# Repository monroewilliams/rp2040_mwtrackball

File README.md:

# rp2040-based trackball main board

This work is based on version 2 of the "rp2040 Minimal KiCad" sample provided by the Raspberry Pi foundation [here](https://datasheets.raspberrypi.com/rp2040/Minimal-KiCAD.zip).

It is inspired by (although not directly based on) jfedor2's excellent [RP2040+PMW3360 board](https://github.com/jfedor2/rp2040-pmw3360). (Although I did borrow the USB header pinout directly from that project.)

I've modified it for the specific needs of [my trackball design](https://github.com/monroewilliams/trackball), with a few other additions that may make it useful for other experimentation as well. I intend it to pair with a [breakout board design](https://github.com/monroewilliams/pmw3360-breakout) with matching JST plugs so that off-the-shelf cables can be used for assembly (instead of the hand-built sensor cables the old design needed).

The overall dimensions of the board match the dimensions of the mini-breadboard I used in the original trackball design. This is not a coincidence. ;) 

The SPI connectors are 6 pin JST-SH (1.0mm pitch), with a pinout based on [Pmod type 2](https://en.wikipedia.org/wiki/Pmod_Interface). This should match the connectors on the sensor breakout board linked above, allowing assembly using off-the-shelf 6-pin JST-SH cables. The cables need to be straight-through, not "crossed" (i.e. connect pin 1 to pin 1, etc.). I've included two SPI connectors attached to one set of SPI pins but with distinct cable select lines (labelled SPI0.x), and a third connector attached to a second set of SPI pins (SPI1.x). The number after the decimal point is the GPIO number of the cable select pin routed to each connector. The trackball design works fine with both sensors on the same SPI bus, but I expect the second bus may be useful for other experiments (such as connecting a display), and I wanted to have some flexibility to play with that.

The button connectors are also JST-SH, but just two pins each (signal and ground), with the intention that off-the-shelf "pigtail" JST cables can be soldered to microswitches for assembly. They are labelled with the number of the GPIO pin they're connected to.

There's also an on-board surface mount piezo speaker, which my trackball design uses to generate scrolling clicks when using twist-to-scroll. It should be usable for other speaker-related duties as needed.

Additionally, I added a connector that is compatible with Adafruit's ["STEMMA QT" I2C connection](https://learn.adafruit.com/introducing-adafruit-stemma-qt/what-is-stemma), and an additional 6 pin JST-SH breakout connector for a few of the other unused pins on the rp2040 (GPIOs 26-29, which happen to be the ADC-capable pins, as well as power and ground).

The final connector is a SWD debug plug that should conform to the [Raspberry Pi 3-pin Debug Connector Specification](https://datasheets.raspberrypi.com/debug/debug-connector-specification.pdf)

And just to finish things off, I included a NeoPixel (a.k.a. WS2812) RGB LED. Adding this to the board bumps it from JLCPCB's "Economic" tier to their "Standard" tier, which is a bit more expensive, so if you're having a batch of these made and would rather go the cheaper route it can just be omitted (just choose not to place it when reviewing the BOM after upload).  This same component is sold in packs of 10 by Adafruit [here](https://www.adafruit.com/product/4684), so it could be added after the fact (assuming you're willing to hand-solder a 2mm square SMD component).

Any issues with the changes I made to this layout are solely my fault. I've attempted to maintain the spirit of the rp2040 reference design, but this is my first attempt at designing a board with a microcontroller, so it would not surprise me if it has problems. Caveat emptor, etc, etc.

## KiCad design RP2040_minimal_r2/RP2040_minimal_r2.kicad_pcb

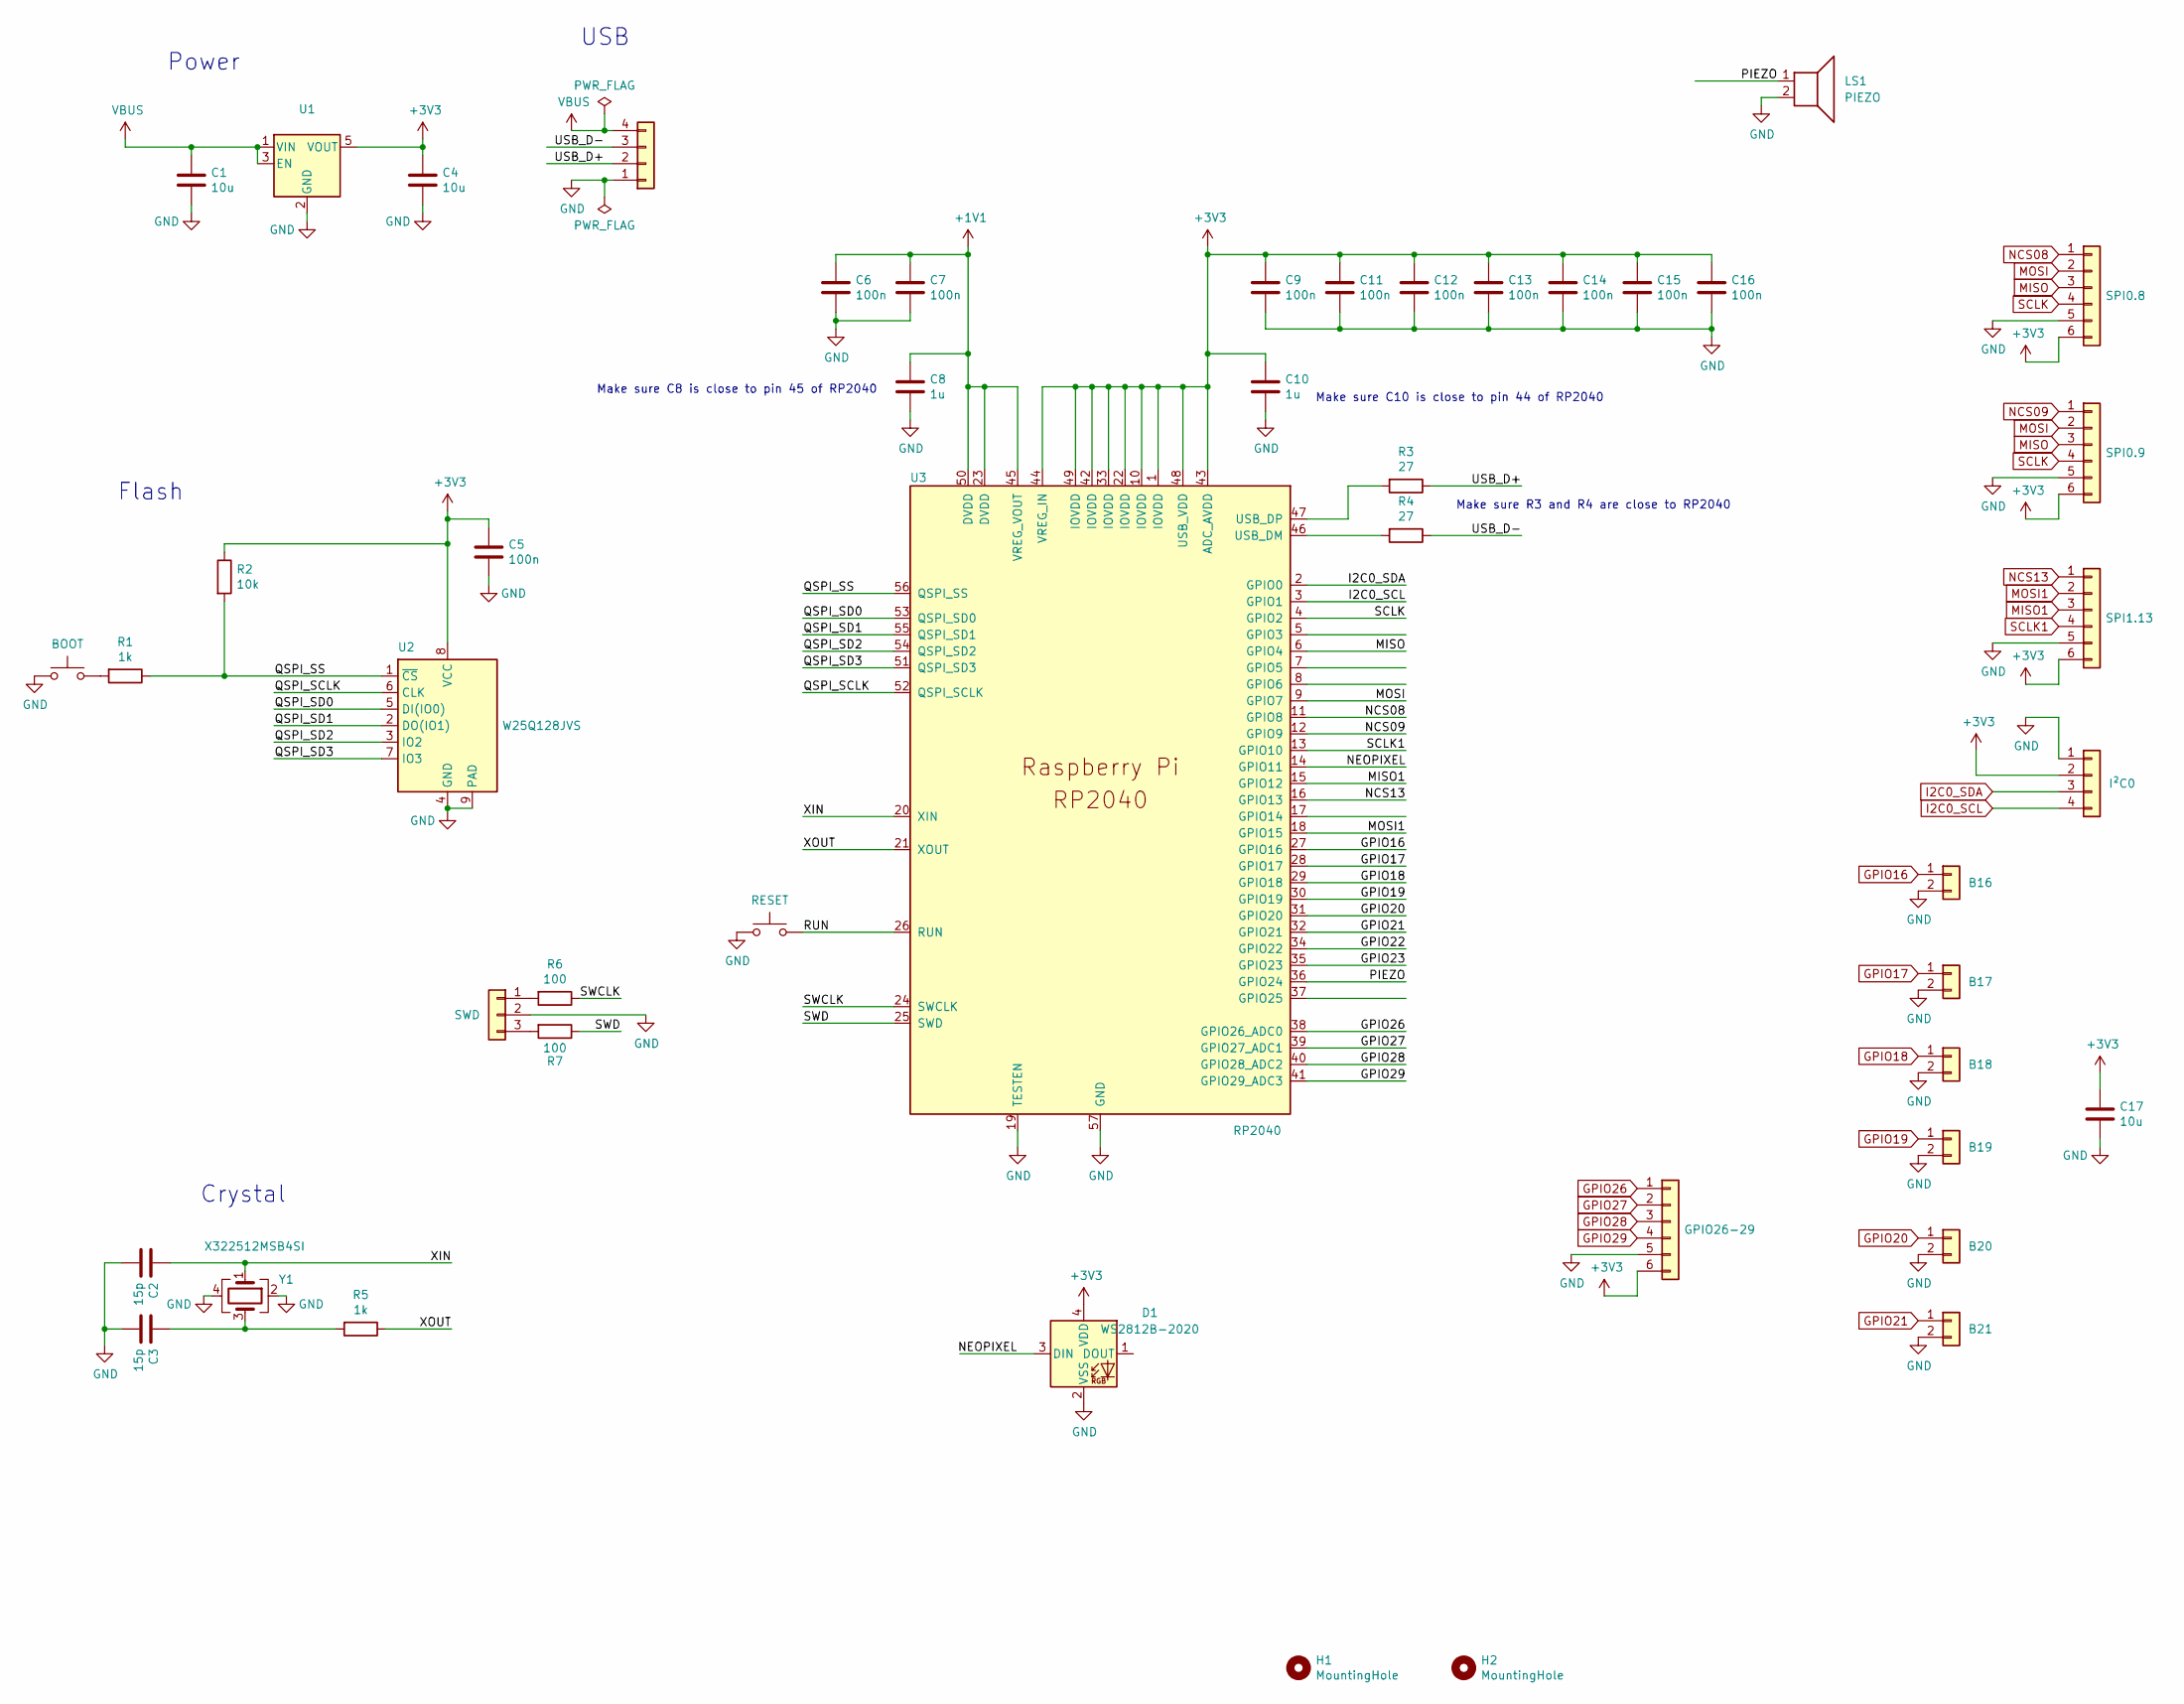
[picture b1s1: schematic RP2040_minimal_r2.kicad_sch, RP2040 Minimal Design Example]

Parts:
C1, C4, C17: 10u; C_0805_2012Metric; LCSC C15850
C2, C3: 15p; C_0402_1005Metric; LCSC C1548
C5, C6, C7, C9, C11, C12, C13, C14, C15, C16: 100n; C_0402_1005Metric; LCSC C126504
C8, C10: 1u; C_0402_1005Metric; LCSC C307331
D1: WS2812B-2020; LED_WS2812B-2020_PLCC4_2.0x2.0mm; LCSC C965555
H1, H2: MountingHole; MountingHole_2.2mm_M2
J1: SPI0.8; JST_SH_BM06B-SRSS-TB_1x06-1MP_P1.00mm_Vertical; LCSC C7430455
J2: SPI0.9; JST_SH_BM06B-SRSS-TB_1x06-1MP_P1.00mm_Vertical; LCSC C7430455
J3: SPI1.13; JST_SH_BM06B-SRSS-TB_1x06-1MP_P1.00mm_Vertical; LCSC C7430455
J4: I²C0; JST_SH_BM04B-SRSS-TB_1x04-1MP_P1.00mm_Vertical; LCSC C160390
J5: USB; JST_XH_B4B-XH-A_1x04_P2.50mm_Vertical; LCSC C7429634
J6: B16; JST_SH_BM02B-SRSS-TB_1x02-1MP_P1.00mm_Vertical; LCSC C160388
J7: B17; JST_SH_BM02B-SRSS-TB_1x02-1MP_P1.00mm_Vertical; LCSC C160388
J8: B18; JST_SH_BM02B-SRSS-TB_1x02-1MP_P1.00mm_Vertical; LCSC C160388
J9: B19; JST_SH_BM02B-SRSS-TB_1x02-1MP_P1.00mm_Vertical; LCSC C160388
J10: B20; JST_SH_BM02B-SRSS-TB_1x02-1MP_P1.00mm_Vertical; LCSC C160388
J11: B21; JST_SH_BM02B-SRSS-TB_1x02-1MP_P1.00mm_Vertical; LCSC C160388
J12: GPIO26-29; JST_SH_BM06B-SRSS-TB_1x06-1MP_P1.00mm_Vertical; LCSC C7430455
J13: SWD; JST_SH_BM03B-SRSS-TB_1x03-1MP_P1.00mm_Vertical; LCSC C160389
LS1: PIEZO; Buzzer_Murata_PKMCS0909E; LCSC C910763
R1, R5: 1k; R_0402_1005Metric; LCSC C11702
R2: 10k; R_0402_1005Metric; LCSC C25744
R3, R4: 27; R_0402_1005Metric; LCSC C274349
R6, R7: 100; R_0402_1005Metric; LCSC C25076
SW1: BOOT; SW_SPST_B3U-1000P; LCSC C498294
SW2: RESET; SW_SPST_B3U-1000P; LCSC C498294
U1: AP2112K-3.3TRG1; SOT-23-5; LCSC C51118
U2: W25Q128JVS; WSON-8-1EP_6x5mm_P1.27mm_EP3.4x4.3mm; LCSC C190862
U3: RP2040; RP2040-QFN-56; LCSC C2040
Y1: X322512MSB4SI; Crystal_SMD_3225-4Pin_3.2x2.5mm; LCSC C9002

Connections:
+1V1: C6.1, C7.1, C8.1, U3.23 (DVDD), U3.45 (VREG_VOUT), U3.50 (DVDD)
+3V3: C4.1, C5.1, C9.1, C10.1, C11.1, C12.1, C13.1, C14.1, C15.1, C16.1, C17.1, D1.4 (VDD), J1.6, J2.6, J3.6, J4.2, J12.6, R2.1, U1.5 (VOUT), U2.8 (VCC), U3.1 (IOVDD), U3.10 (IOVDD), U3.22 (IOVDD), U3.33 (IOVDD), U3.42 (IOVDD), U3.43 (ADC_AVDD), U3.44 (VREG_IN), U3.48 (USB_VDD), U3.49 (IOVDD)
/GPIO22: U3.34 (GPIO22)
/GPIO23: U3.35 (GPIO23)
/NEOPIXEL: D1.3 (DIN), U3.14 (GPIO11)
/PIEZO: LS1.1, U3.36 (GPIO24)
/QSPI_SCLK: U2.6 (CLK), U3.52 (QSPI_SCLK)
/QSPI_SD0: U2.5 (DI(IO0)), U3.53 (QSPI_SD0)
/QSPI_SD1: U2.2 (DO(IO1)), U3.55 (QSPI_SD1)
/QSPI_SD2: U2.3 (IO2), U3.54 (QSPI_SD2)
/QSPI_SD3: U2.7 (IO3), U3.51 (QSPI_SD3)
/QSPI_SS: R1.1, R2.2, U2.1 (~CS), U3.56 (QSPI_SS)
/RUN: SW2.2, U3.26 (RUN)
/SWCLK: R6.1, U3.24 (SWCLK)
/SWD: R7.1, U3.25 (SWD)
/USB_D+: J5.2, R3.1
/USB_D-: J5.3, R4.1
/XIN: C2.1, U3.20 (XIN), Y1.1
/XOUT: R5.1, U3.21 (XOUT)
GND: C1.2, C2.2, C3.2, C4.2, C5.2, C6.2, C7.2, C8.2, C9.2, C10.2, C11.2, C12.2, C13.2, C14.2, C15.2, C16.2, C17.2, D1.2 (VSS), J1.5, J2.5, J3.5, J4.1, J5.1, J6.2, J7.2, J8.2, J9.2, J10.2, J11.2, J12.5, J13.2, LS1.2, SW1.1, SW2.1, U1.2 (GND), U2.4 (GND), U2.9 (PAD), U3.19 (TESTEN), U3.57 (GND), Y1.2, Y1.4
GPIO16: J6.1, U3.27 (GPIO16)
GPIO17: J7.1, U3.28 (GPIO17)
GPIO18: J8.1, U3.29 (GPIO18)
GPIO19: J9.1, U3.30 (GPIO19)
GPIO20: J10.1, U3.31 (GPIO20)
GPIO21: J11.1, U3.32 (GPIO21)
GPIO26: J12.1, U3.38 (GPIO26_ADC0)
GPIO27: J12.2, U3.39 (GPIO27_ADC1)
GPIO28: J12.3, U3.40 (GPIO28_ADC2)
GPIO29: J12.4, U3.41 (GPIO29_ADC3)
I2C0_SCL: J4.4, U3.3 (GPIO1)
I2C0_SDA: J4.3, U3.2 (GPIO0)
MISO: J1.3, J2.3, U3.6 (GPIO4)
MISO1: J3.3, U3.15 (GPIO12)
MOSI: J1.2, J2.2, U3.9 (GPIO7)
MOSI1: J3.2, U3.18 (GPIO15)
NCS08: J1.1, U3.11 (GPIO8)
NCS09: J2.1, U3.12 (GPIO9)
NCS13: J3.1, U3.16 (GPIO13)
unnamed: C3.1, R5.2, Y1.3
unnamed: J13.1, R6.2
unnamed: J13.3, R7.2
unnamed: R1.2, SW1.2
unnamed: R4.2, U3.46 (USB_DM)
unnamed: R3.2, U3.47 (USB_DP)
SCLK: J1.4, J2.4, U3.4 (GPIO2)
SCLK1: J3.4, U3.13 (GPIO10)
VBUS: C1.1, J5.4, U1.1 (VIN), U1.3 (EN)

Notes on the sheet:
Power
Crystal
Make sure C8 is close to pin 45 of RP2040
Make sure C10 is close to pin 44 of RP2040
USB
Make sure R3 and R4 are close to RP2040
Flash

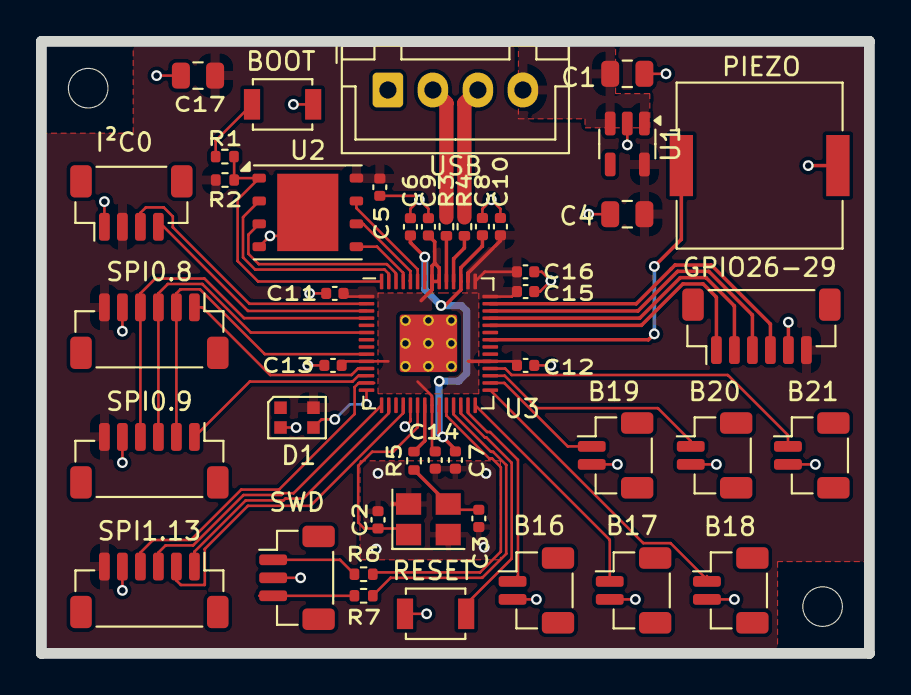
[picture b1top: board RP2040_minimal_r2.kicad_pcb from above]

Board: 2 copper layers, 46.0 x 34.0 mm, 47 parts (0 on the bottom side), 46 nets.

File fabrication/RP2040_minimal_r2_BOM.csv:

"Designator","Comment","Footprint","DNP","LCSC"
"Y1","X322512MSB4SI","Crystal:Crystal_SMD_3225-4Pin_3.2x2.5mm","","C9002"
"U3","RP2040","RP2040_minimal:RP2040-QFN-56","","C2040"
"U2","W25Q128JVS","RP2040_minimal:WSON-8-1EP_6x5mm_P1.27mm_EP3.4x4.3mm","","C190862"
"U1","AP2112K-3.3TRG1","RP2040_minimal:SOT-23-5","","C51118"
"SW1,SW2","-- mixed values --","Button_Switch_SMD:SW_SPST_B3U-1000P","","C498294"
"R6,R7","100","Resistor_SMD:R_0402_1005Metric","","C25076"
"R3,R4","27","Resistor_SMD:R_0402_1005Metric","","C274349"
"R2","10k","Resistor_SMD:R_0402_1005Metric","","C25744"
"R1,R5","1k","Resistor_SMD:R_0402_1005Metric","","C11702"
"LS1","PIEZO","Buzzer_Beeper:Buzzer_Murata_PKMCS0909E","","C910763"
"J13","SWD","RP2040_minimal:JST_SH_BM03B-SRSS-TB_1x03-1MP_P1.00mm_Vertical","","C160389"
"J6,J7,J8,J9,J10,J11","-- mixed values --","RP2040_minimal:JST_SH_BM02B-SRSS-TB_1x02-1MP_P1.00mm_Vertical","","C160388"
"J5","USB","RP2040_minimal:JST_XH_B4B-XH-A_1x04_P2.50mm_Vertical","","C7429634"
"J4","I²C0","Connector_JST:JST_SH_BM04B-SRSS-TB_1x04-1MP_P1.00mm_Vertical","","C160390"
"J1,J2,J3,J12","-- mixed values --","RP2040_minimal:JST_SH_BM06B-SRSS-TB_1x06-1MP_P1.00mm_Vertical","","C7430455"
"D1","WS2812B-2020","LED_SMD:LED_WS2812B-2020_PLCC4_2.0x2.0mm","","C965555"
"C8,C10","1u","Capacitor_SMD:C_0402_1005Metric","","C307331"
"C5,C6,C7,C9,C11,C12,C13,C14,C15,C16","100n","Capacitor_SMD:C_0402_1005Metric","","C126504"
"C2,C3","15p","Capacitor_SMD:C_0402_1005Metric","","C1548"
"C1,C4,C17","10u","Capacitor_SMD:C_0805_2012Metric","","C15850"

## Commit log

2024-12-26 Initial import from https://datasheets.raspberrypi.com/rp2040/Minimal-KiCAD.zip Re-saved with current version of KiCad (8.0.7) Added "LCSC" field name to hold JLCPCB part numbers. Assigned JLCPCB par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
    NOTE that the column labels in the placement file are hard-coded, so these still have to be edited manually after every export before JLCPCB can process them.
    JLPCB wants these column names in the CPL (a.k.a. all-pos) file:
    Designator,Val,Package,Mid X, Mid Y,Rotation,Layer
2024-12-28 Reshape board to 46x34mm to match the footprint of the old breadboard. Replace some components (voltage regulator, flash memory chip, crystal) with ones that are cheaper and/or smaller Add BOOT/RESET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
2024-12-28 Change connectors to JST-SH 1.0mm Additional routing tweaks.
2024-12-28 Add I2C/STEMMA QT connector
2024-12-28 Added 6 button connectors. Added 6 pin breakout for GPIO 26-29 (includes ground and +3.3v as well).
2025-01-02 Update gerbers and BOM/placement files. Add readme file. Add github url to rear silkscreen layer. Clean up some old unused fill zones that I'd moved off to the side.
2025-01-03 Added a WS2812 LED (a.k.a. NeoPixel) Removed some top-side ground traces in favor of vias closer to ground pads. Updated the github URL. Minor changes to the readme.
2025-01-06 Fix incorrect pins used for SPI0. Changed button pins to GPIO 16-21 for slightly cleaner layout. Moved USB header closer to board edge, to allow JST-XH connector to be attached the other way around. 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
2025-01-15 Minor fixes to BOM generation settings.
2025-01-16 Update the USB connection to use a proper JST-XH footprint. Add local copies of several footprints that need to be tweaked to match JLCPCB's notion of component orientation/origin.
2025-01-16 Add SWD debug connector.
2025-01-16 Updates to README
2025-01-19 Add a board variant, and example code that demonstrates how to use it with VS Code/PlatformIO.
